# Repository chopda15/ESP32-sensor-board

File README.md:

# ESP32-C3 IoT Sensor Board with Li-ion Power Management

Custom-designed IoT PCB built in KiCad featuring the ESP32-C3-WROOM-02 module, integrated Li-ion charging circuitry, environmental sensing, onboard storage, and USB-C connectivity.

This project was developed to practice real-world embedded hardware design workflows including schematic capture, PCB layout, signal integrity considerations, power management, DFM validation, and manufacturing preparation.

---

# Features

## Microcontroller
- ESP32-C3-WROOM-02
- Wi-Fi + BLE connectivity
- Low-power IoT architecture

## Power System
- TP4056 Li-ion battery charger
- USB-C power input
- Single-cell LiPo battery support
- Battery charging and protection circuitry
- 3.3V regulated power rail

## Sensors & Peripherals
- BME280 environmental sensor
  - Temperature
  - Humidity
  - Pressure
- Ambient light sensor
- Sound sensor with microphone amplifier
- OLED display via I2C
- SPI flash memory
- Micro SD card interface

## User Interface
- Status LEDs
- Push buttons
- USB-UART interface for programming/debugging

---

# PCB Design Highlights

## Signal Integrity
- Differential routing for USB signals
- SPI trace optimization
- Reduced trace lengths for high-speed signals
- Ground plane implementation
- Decoupling capacitor placement optimization

## Power Distribution
- Copper pours for stable power delivery
- Wide power traces to minimize voltage drop
- Multiple decoupling capacitors for noise reduction

## Manufacturing Considerations
- ERC and DRC validation
- DFM analysis before fabrication
- Gerber generation
- BOM and centroid file generation
- Silkscreen refinement
- 3D PCB validation

---

# Tools & Technologies

- KiCad 9
- ESP32-C3
- TP4056
- JLCPCB DFM tools
- Git & GitHub

---

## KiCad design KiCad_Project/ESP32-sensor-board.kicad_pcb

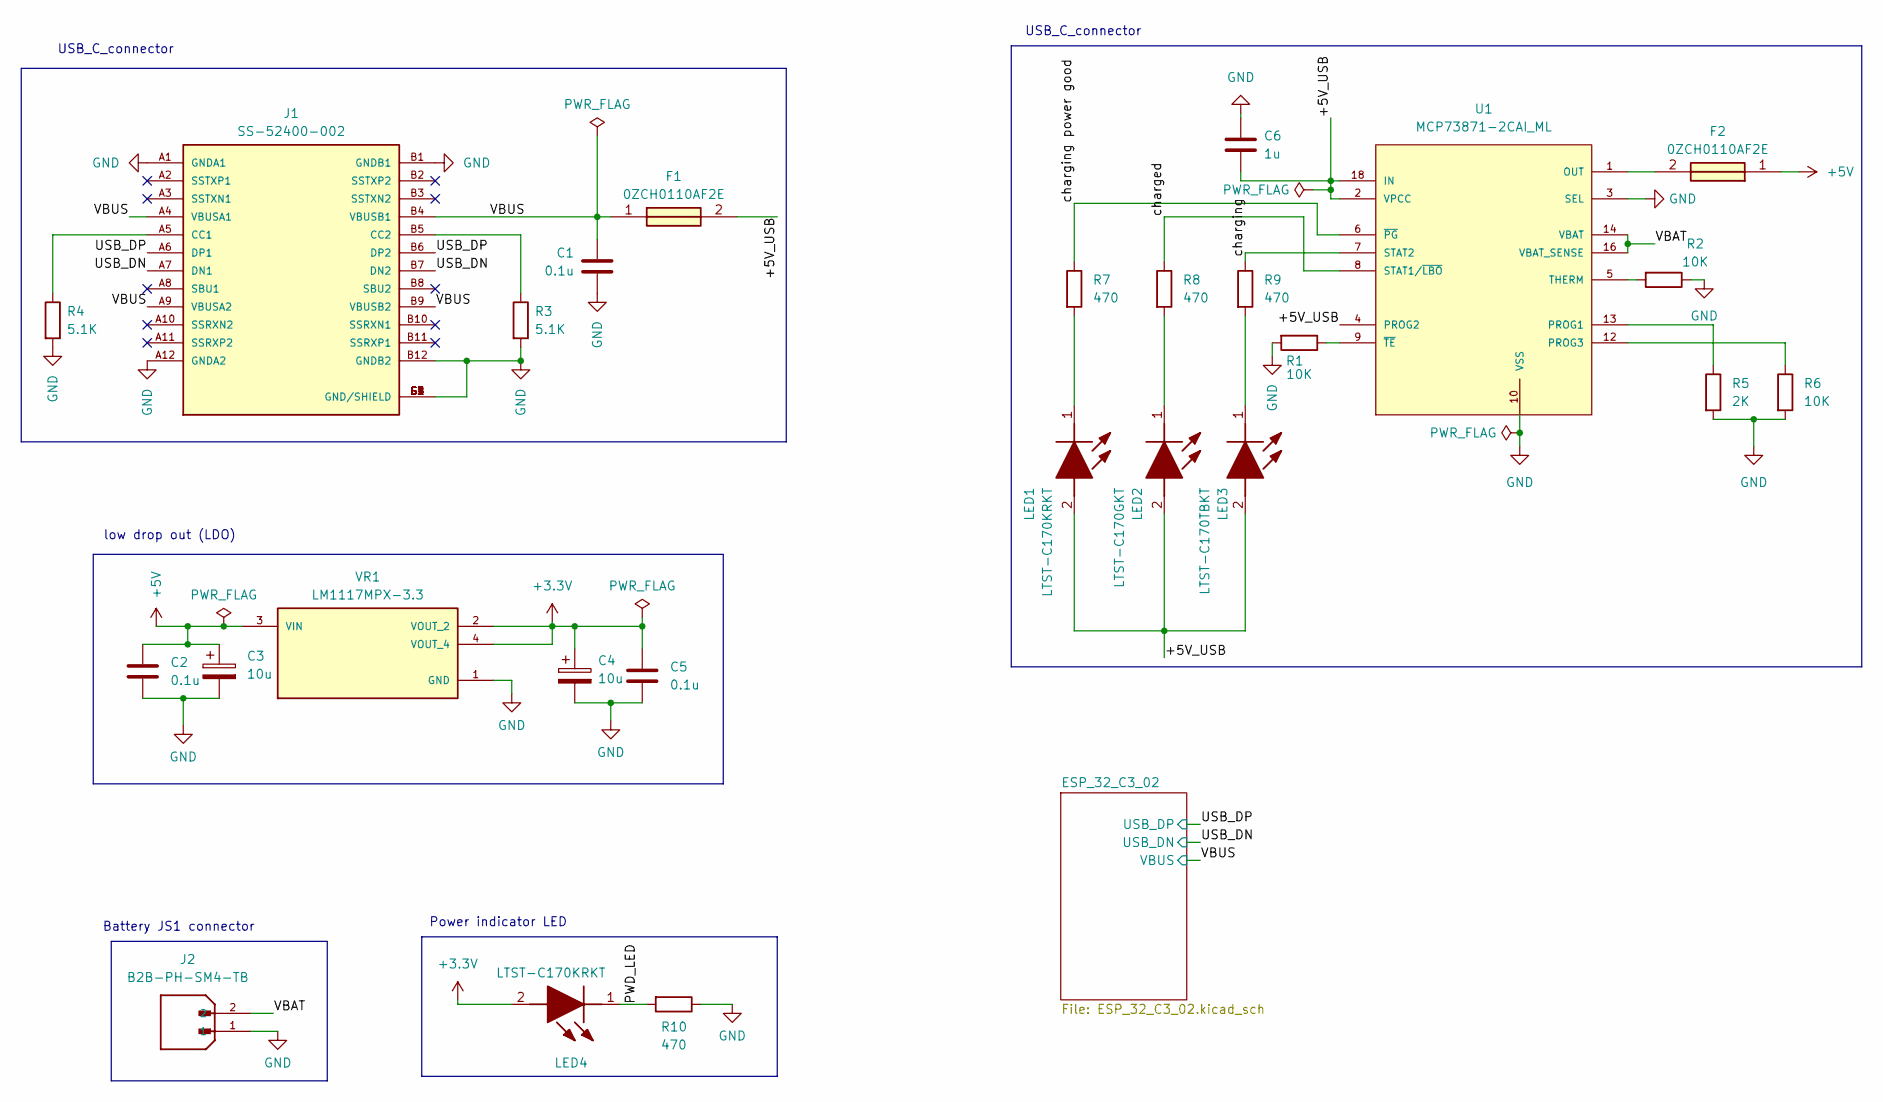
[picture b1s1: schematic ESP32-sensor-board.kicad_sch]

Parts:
C1, C2, C5: 0.1u; C_0805_2012Metric
C3, C4: 10u; T491A
C6: 1u; C_0805_2012Metric
F1, F2: 0ZCH0110AF2E; FUSC3226X100N; Manufacturer_Part_Number 0ZCH0110AF2E
J1: SS-52400-002; BELFUSE_SS-52400-002; PARTREV A0
J2: B2B-PH-SM4-TB; JST_B2B-PH-SM4-TB; PARTREV N/A
LED1, LED4: LTST-C170KRKT; LEDC2012X120N; Manufacturer_Part_Number LTST-C170KRKT; Mouser Part Number 859-LTST-C170KRKT
LED2: LTST-C170GKT; LEDC2012X120N; Manufacturer_Part_Number LTST-C170GKT; Mouser Part Number 859-LTST-C170GKT
LED3: LTST-C170TBKT; LEDC2012X120N; Manufacturer_Part_Number LTST-C170TBKT; Mouser Part Number 859-LTST-C170TBKT
R1, R2, R6: 10K; R_0805_2012Metric
R3, R4: 5.1K; R_0805_2012Metric
R5: 2K; R_0805_2012Metric
R7, R8, R9, R10: 470; R_0805_2012Metric
U1: MCP73871-2CAI_ML; QFN50P400X400X100-21N; PARTREV D
VR1: LM1117MPX-3.3; VREG_LM1117MPX-3.3_NOPB

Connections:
+3.3V: C4.1, C5.1, LED4.2 (A), VR1.2 (VOUT_2), VR1.4 (VOUT_4); also elsewhere on the board
+5V: C2.1, C3.1, F2.1, U1.19, VR1.3 (VIN)
/+5V_USB: C6.2, F1.2, LED1.2 (A), LED2.2 (A), LED3.2 (A), U1.2 (VPCC), U1.4 (PROG2), U1.18 (IN)
/PWD_LED: LED4.1 (K), R10.2
/USB_DN: J1.A7 (DN1), J1.B7 (DN2); also elsewhere on the board
/USB_DP: J1.A6 (DP1), J1.B6 (DP2); also elsewhere on the board
/VBAT: J2.2, U1.14 (VBAT), U1.16 (VBAT_SENSE)
/VBUS: C1.1, F1.1, J1.A4 (VBUSA1), J1.A9 (VBUSA2), J1.B4 (VBUSB1), J1.B9 (VBUSB2); also elsewhere on the board
/charged: R8.1, U1.8 (STAT1/~LBO)
/charging: R9.1, U1.7 (STAT2)
/charging power good: R7.1, U1.6 (~PG)
GND: C1.2, C2.2, C3.2, C4.2, C5.2, C6.1, J1.A1 (GNDA1), J1.A12 (GNDA2), J1.B1 (GNDB1), J1.B12 (GNDB2), J1.G1 (GND/SHIELD), J1.G2 (GND/SHIELD), J1.G3 (GND/SHIELD), J1.G4 (GND/SHIELD), J1.S1 (GND/SHIELD), J1.S2 (GND/SHIELD), J1.S3 (GND/SHIELD), J1.S4 (GND/SHIELD), J2.1, R1.2, R2.1, R3.2, R4.2, R5.2, R6.2, R10.1, U1.3 (SEL), U1.10 (VSS), U1.21, VR1.1 (GND); also elsewhere on the board
unnamed: J1.A5 (CC1), R4.1
unnamed: J1.B5 (CC2), R3.1
unnamed: LED1.1 (K), R7.2
unnamed: LED2.1 (K), R8.2
unnamed: LED3.1 (K), R9.2
unnamed: F2.2, U1.1 (OUT)
unnamed: R5.1, U1.13 (PROG1)
unnamed: R6.1, U1.12 (PROG3)
unnamed: R2.2, U1.5 (THERM)
unnamed: R1.1, U1.9 (~TE)

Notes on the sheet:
USB_C_connector
Battery JS1 connector
low drop out (LDO)
Power indicator LED

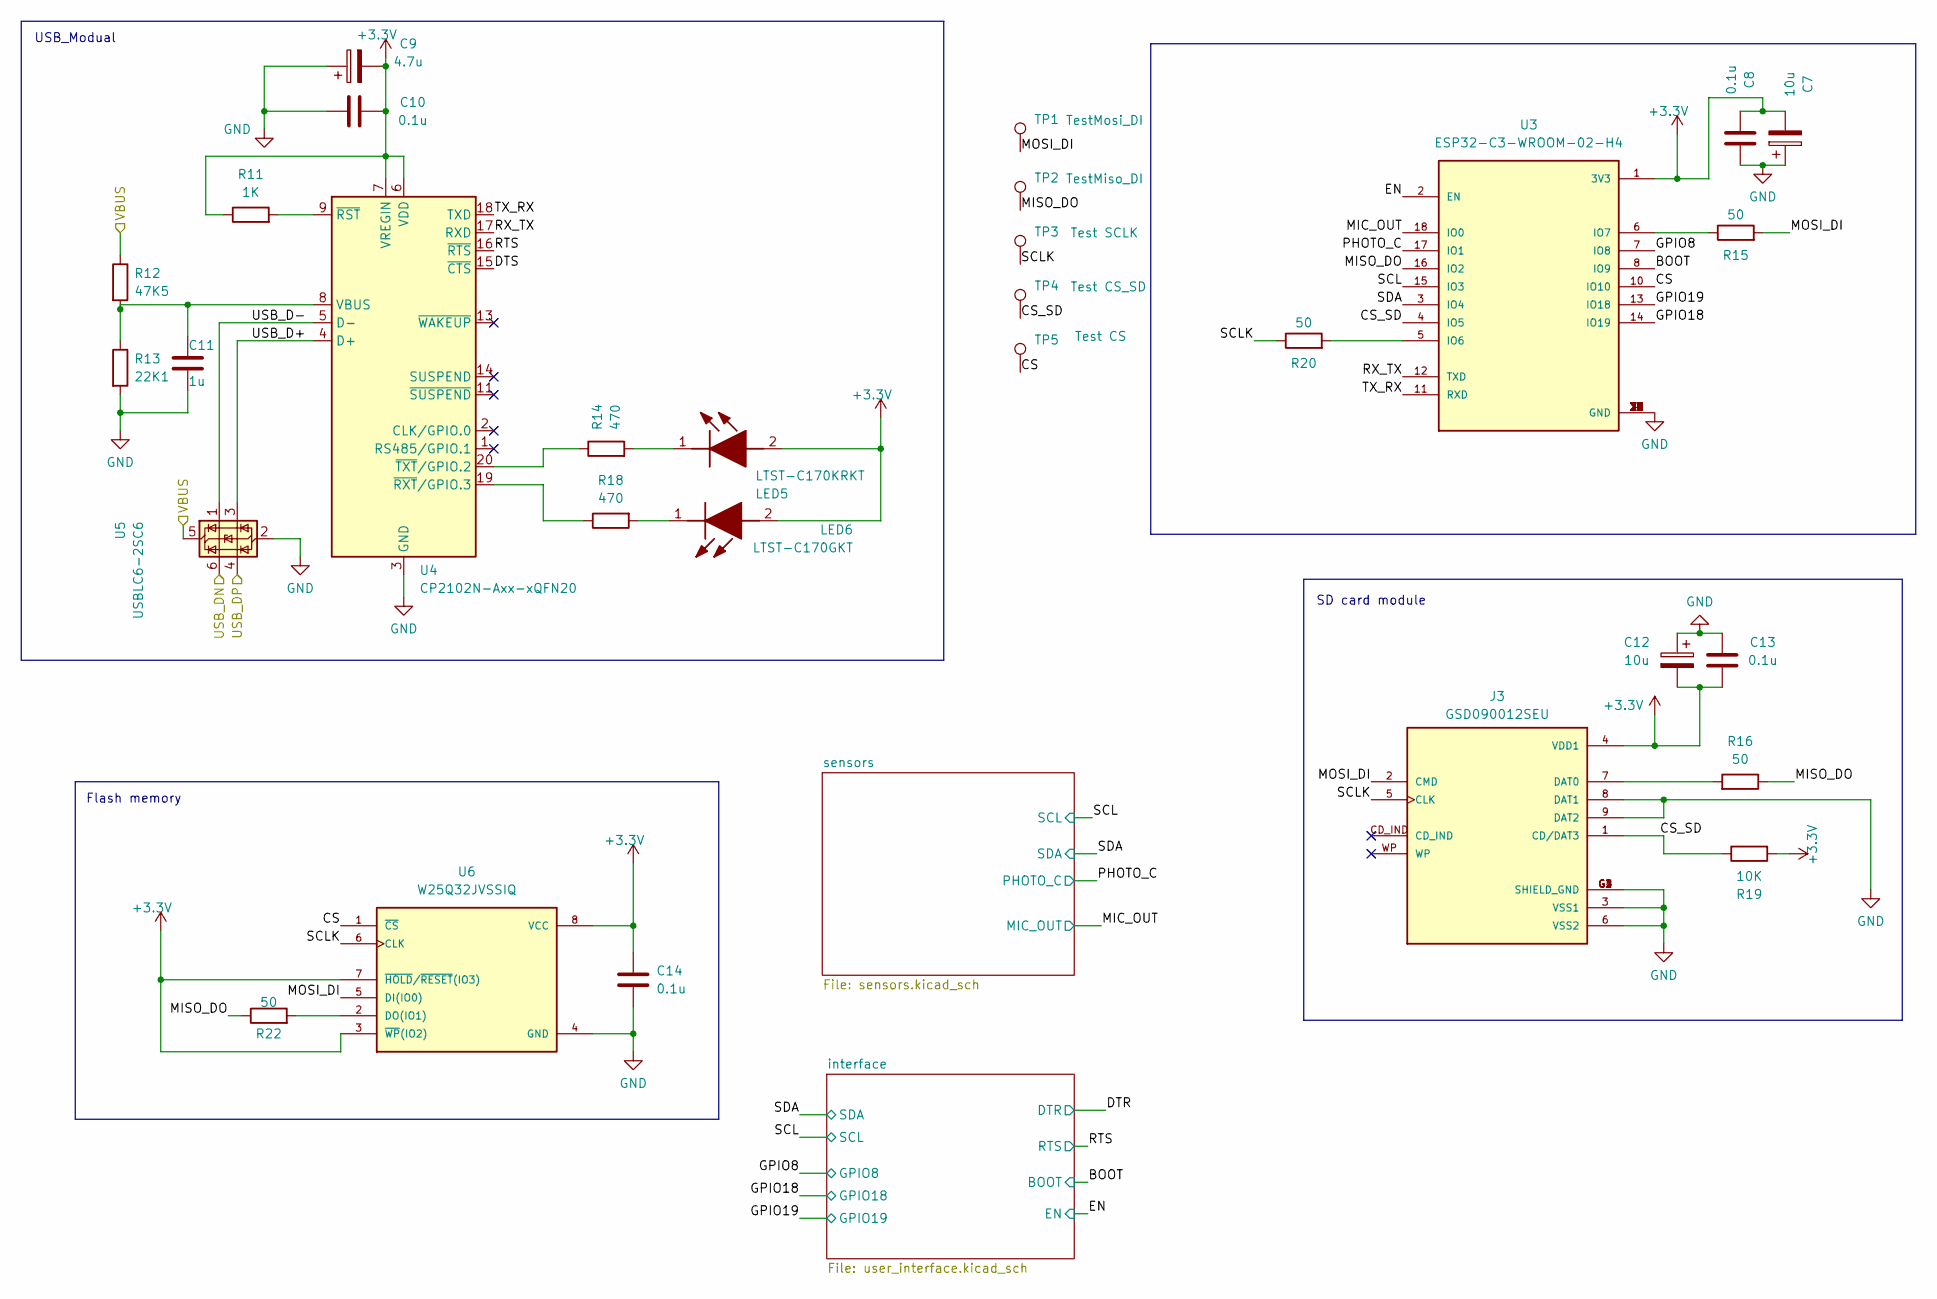
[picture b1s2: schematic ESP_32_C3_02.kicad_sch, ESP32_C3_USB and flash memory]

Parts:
C7, C12: 10u; T491A
C8, C10, C13, C14: 0.1u; C_0805_2012Metric
C9: 4.7u; T491A
C11: 1u; C_0805_2012Metric
J3: GSD090012SEU; AMPHENOL_GSD090012SEU; PARTREV E
LED5: LTST-C170KRKT; LEDC2012X120N; Manufacturer_Part_Number LTST-C170KRKT; Mouser Part Number 859-LTST-C170KRKT
LED6: LTST-C170GKT; LEDC2012X120N; Manufacturer_Part_Number LTST-C170GKT; Mouser Part Number 859-LTST-C170GKT
R11: 1K; R_0805_2012Metric
R12: 47K5; R_0805_2012Metric
R13: 22K1; R_0805_2012Metric
R14, R18: 470; R_0805_2012Metric
R15, R16, R20, R22: 50; R_0805_2012Metric
R19: 10K; R_0805_2012Metric
TP1: TestMosi_DI; TestPoint_Pad_D1.0mm
TP2: TestMiso_DI; TestPoint_Pad_D1.0mm
TP3: Test SCLK; TestPoint_Pad_D1.0mm
TP4: Test CS_SD; TestPoint_Pad_D1.0mm
TP5: Test CS; TestPoint_Pad_D1.0mm
U3: ESP32-C3-WROOM-02-H4; MODULE_ESP32-C3-WROOM-02-H4
U4: CP2102N-Axx-xQFN20; SiliconLabs_QFN-20-1EP_3x3mm_P0.5mm_EP1.8x1.8mm
U5: USBLC6-2SC6; SOT-23-6
U6: W25Q32JVSSIQ; SOIC127P790X216-8N; M_PART_NUMBER W25QXX

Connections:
+3.3V: C7.2, C8.2, C9.2, C10.2, C12.2, C13.2, C14.1, J3.4 (VDD1), LED5.2 (A), LED6.2 (A), R11.1, R19.2, U3.1 (3V3), U4.6 (VDD), U4.7 (VREGIN), U6.3 (~WP(IO2)), U6.7 (~HOLD/~RESET(IO3)), U6.8 (VCC); also elsewhere on the board
/ESP_32_C3_02/BOOT: U3.8 (IO9); also elsewhere on the board
/ESP_32_C3_02/CS: TP5.1 (1_1), U3.10 (IO10), U6.1 (~CS)
/ESP_32_C3_02/CS_SD: J3.1 (CD/DAT3), R19.1, TP4.1 (1_1), U3.4 (IO5)
/ESP_32_C3_02/DTS: U4.15 (~CTS)
/ESP_32_C3_02/EN: U3.2 (EN); also elsewhere on the board
/ESP_32_C3_02/GPIO8: U3.7 (IO8); also elsewhere on the board
/ESP_32_C3_02/GPIO18: U3.14 (IO19); also elsewhere on the board
/ESP_32_C3_02/GPIO19: U3.13 (IO18); also elsewhere on the board
/ESP_32_C3_02/MIC_OUT: U3.18 (IO0); also elsewhere on the board
/ESP_32_C3_02/MISO_DO: R16.1, R22.1, TP2.1 (1_1), U3.16 (IO2)
/ESP_32_C3_02/MOSI_DI: J3.2 (CMD), R15.2, TP1.1 (1_1), U6.5 (DI(IO0))
/ESP_32_C3_02/PHOTO_C: U3.17 (IO1); also elsewhere on the board
/ESP_32_C3_02/RTS: U4.16 (~RTS); also elsewhere on the board
/ESP_32_C3_02/RX_TX: U3.12 (TXD), U4.17 (RXD)
/ESP_32_C3_02/SCL: U3.15 (IO3); also elsewhere on the board
/ESP_32_C3_02/SCLK: J3.5 (CLK), R20.1, TP3.1 (1_1), U6.6 (CLK)
/ESP_32_C3_02/SDA: U3.3 (IO4); also elsewhere on the board
/ESP_32_C3_02/TX_RX: U3.11 (RXD), U4.18 (TXD)
/ESP_32_C3_02/USB_D+: U4.4 (D+), U5.3 (I/O2)
/ESP_32_C3_02/USB_D-: U4.5 (D-), U5.1 (I/O1)
/USB_DN: U5.6 (I/O1); also elsewhere on the board
/USB_DP: U5.4 (I/O2); also elsewhere on the board
/VBUS: R12.1, U5.5 (VBUS); also elsewhere on the board
GND: C7.1, C8.1, C9.1, C10.1, C11.2, C12.1, C13.1, C14.2, J3.3 (VSS1), J3.6 (VSS2), J3.8 (DAT1), J3.9 (DAT2), J3.G1 (SHIELD_GND), J3.G2 (SHIELD_GND), J3.G3 (SHIELD_GND), J3.G4 (SHIELD_GND), R13.2, U3.9 (GND), U3.19 (GND), U3.20 (GND), U3.21 (GND), U3.22 (GND), U3.23 (GND), U3.24 (GND), U3.25 (GND), U3.26 (GND), U3.27 (GND), U3.28 (GND), U3.29 (GND), U3.30 (GND), U3.31 (GND), U3.32 (GND), U3.33 (GND), U3.34 (GND), U3.35 (GND), U3.36 (GND), U3.37 (GND), U3.38 (GND), U3.39 (GND), U4.3 (GND), U4.12 (GND), U4.21 (GND), U5.2 (GND), U6.4 (GND); also elsewhere on the board
unnamed: J3.7 (DAT0), R16.2
unnamed: LED5.1 (K), R14.2
unnamed: LED6.1 (K), R18.2
unnamed: R20.2, U3.5 (IO6)
unnamed: R15.1, U3.6 (IO7)
unnamed: C11.1, R12.2, R13.1, U4.8 (VBUS)
unnamed: R11.2, U4.9 (~RST)
unnamed: R18.1, U4.19 (~RXT/GPIO.3)
unnamed: R14.1, U4.20 (~TXT/GPIO.2)
unnamed: R22.2, U6.2 (DO(IO1))

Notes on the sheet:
USB_Modual
SD card module
Flash memory

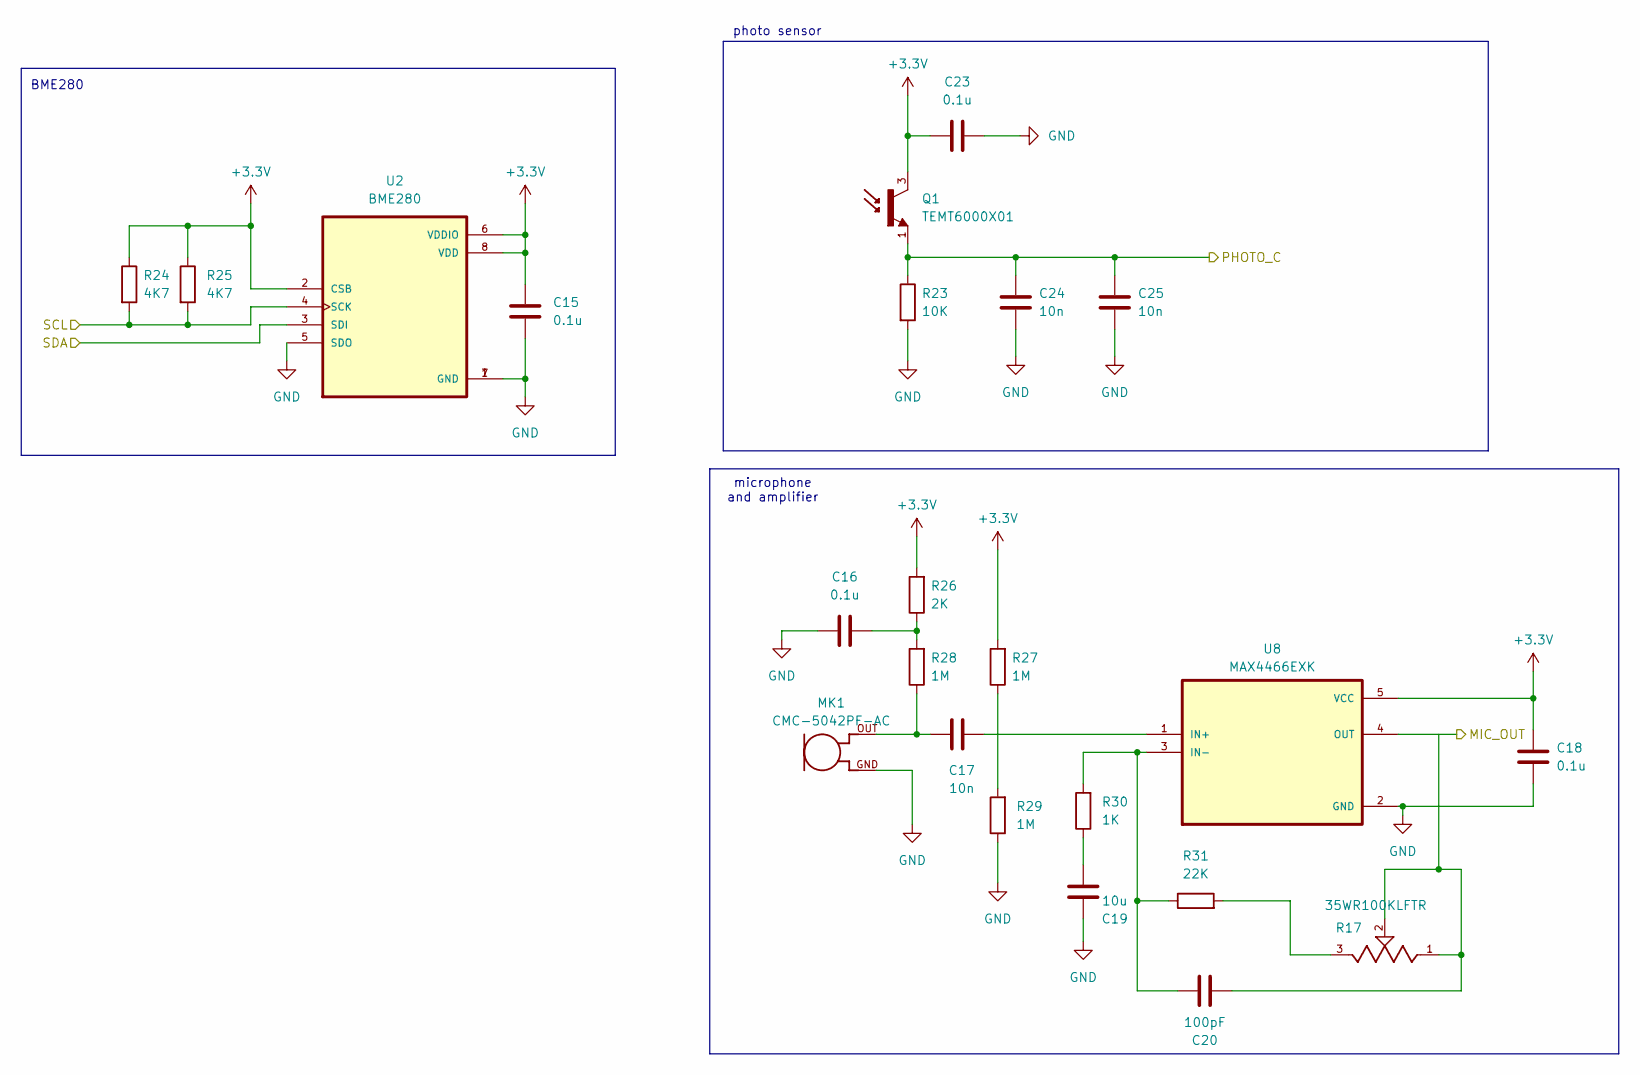
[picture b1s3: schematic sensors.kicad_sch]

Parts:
C15, C16, C18, C23: 0.1u; C_0805_2012Metric
C17, C24, C25: 10n; C_0805_2012Metric
C19: 10u; C_0805_2012Metric
C20: 100pF; C_0805_2012Metric
MK1: CMC-5042PF-AC; CUI_CMC-5042PF-AC
Q1: TEMT6000X01; TRANS_TEMT6000X01; PARTREV 1.9
R17: 35WR100KLFTR; TRIM_35WR100KLFTR; PARTREV D
R23: 10K; R_0805_2012Metric
R24, R25: 4K7; R_0805_2012Metric
R26: 2K; R_0805_2012Metric
R27, R28, R29: 1M; R_0805_2012Metric
R30: 1K; R_0805_2012Metric
R31: 22K; R_0805_2012Metric
U2: BME280; PSON65P250X250X100-8N
U8: MAX4466EXK; SOT65P210X110-5N

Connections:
+3.3V: C15.1, C18.1, C23.1, Q1.3, R24.1, R25.1, R26.2, R27.2, U2.2 (CSB), U2.6 (VDDIO), U2.8 (VDD), U8.5 (VCC); also elsewhere on the board
/ESP_32_C3_02/MIC_OUT: U8.4 (OUT); also elsewhere on the board
/ESP_32_C3_02/PHOTO_C: C24.2, C25.2, Q1.1, R23.1; also elsewhere on the board
/ESP_32_C3_02/SCL: R24.2, R25.2, U2.4 (SCK); also elsewhere on the board
/ESP_32_C3_02/SDA: U2.3 (SDI); also elsewhere on the board
GND: C15.2, C16.1, C18.2, C19.2, C23.2, C24.1, C25.1, MK1.GND, R23.2, R29.1, U2.1 (GND), U2.5 (SDO), U2.7 (GND), U8.2 (GND); also elsewhere on the board
unnamed: C16.2, R26.1, R28.2
unnamed: C17.1, MK1.OUT, R28.1
unnamed: C19.1, R30.1
unnamed: C20.2, R17.1, R17.2
unnamed: R17.3, R31.2
unnamed: R27.1, R29.2
unnamed: C17.2, U8.1 (IN+)
unnamed: C20.1, R30.2, R31.1, U8.3 (IN-)

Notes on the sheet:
BME280
microphone and amplifier
photo sensor

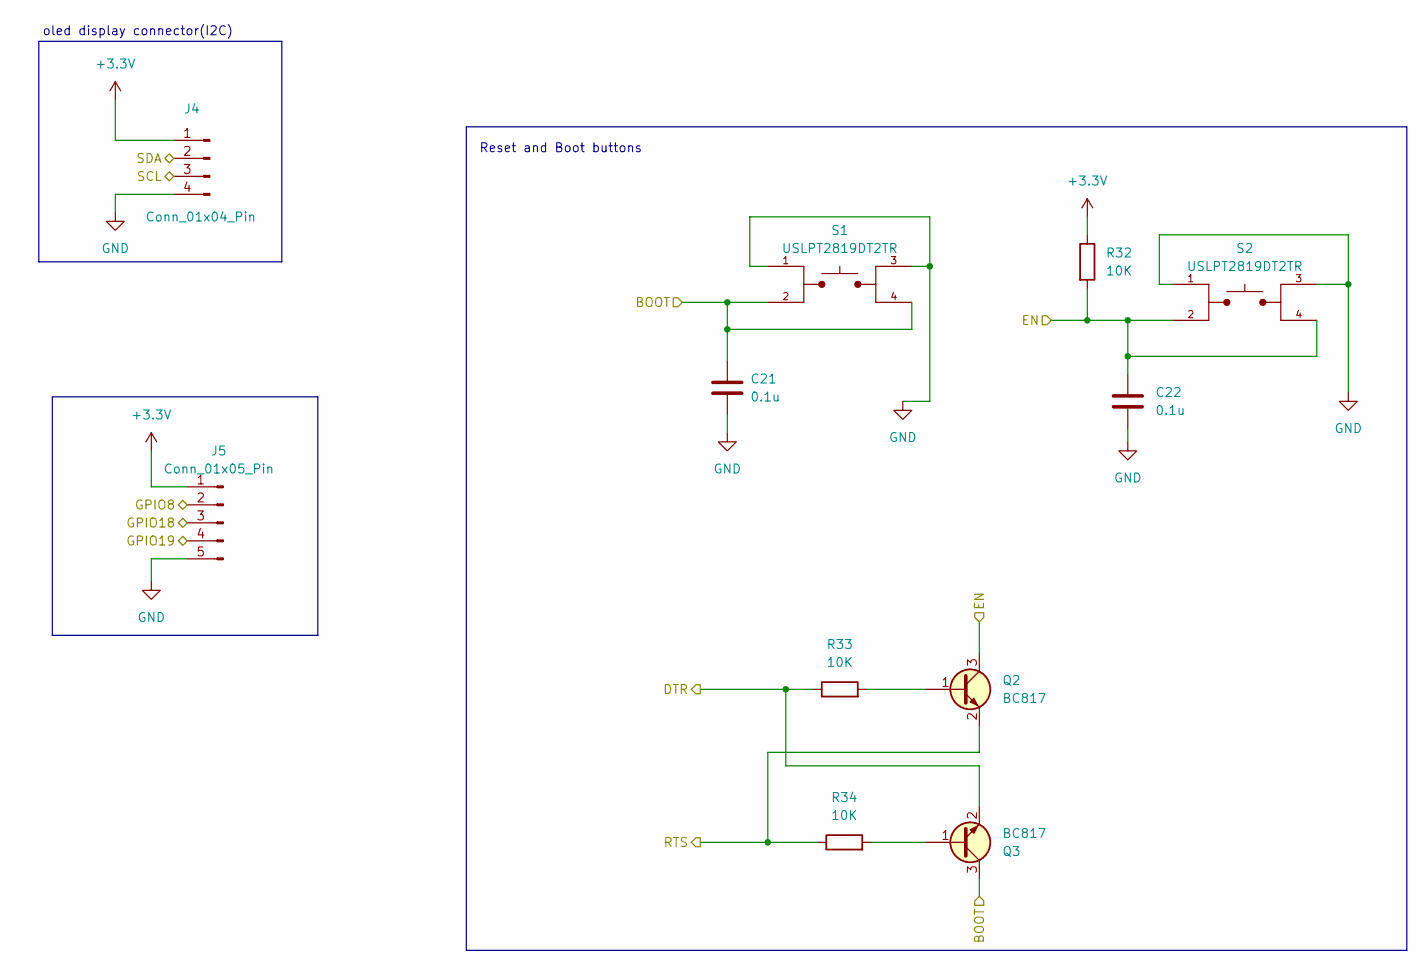
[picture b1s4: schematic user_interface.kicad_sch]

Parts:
C21, C22: 0.1u; C_0805_2012Metric
J4: Conn_01x04_Pin; PinHeader_1x04_P2.54mm_Vertical
J5: Conn_01x05_Pin; PinHeader_1x05_P2.54mm_Vertical
Q2, Q3: BC817; SOT-23
R32, R33, R34: 10K; R_0805_2012Metric
S1, S2: USLPT2819DT2TR; SW_TL3305AF260QG; PARTREV C

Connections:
+3.3V: J4.1, J5.1, R32.1; also elsewhere on the board
/ESP_32_C3_02/BOOT: C21.1, Q3.3 (C), S1.2, S1.4; also elsewhere on the board
/ESP_32_C3_02/DTR: Q3.2 (E), R33.1
/ESP_32_C3_02/EN: C22.1, Q2.3 (C), R32.2, S2.2, S2.4; also elsewhere on the board
/ESP_32_C3_02/GPIO8: J5.2; also elsewhere on the board
/ESP_32_C3_02/GPIO18: J5.3; also elsewhere on the board
/ESP_32_C3_02/GPIO19: J5.4; also elsewhere on the board
/ESP_32_C3_02/RTS: Q2.2 (E), R34.1; also elsewhere on the board
/ESP_32_C3_02/SCL: J4.3; also elsewhere on the board
/ESP_32_C3_02/SDA: J4.2; also elsewhere on the board
GND: C21.2, C22.2, J4.4, J5.5, S1.1, S1.3, S2.1, S2.3; also elsewhere on the board
unnamed: Q2.1 (B), R33.2
unnamed: Q3.1 (B), R34.2

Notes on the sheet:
Reset and Boot buttons
oled display connector(I2C)

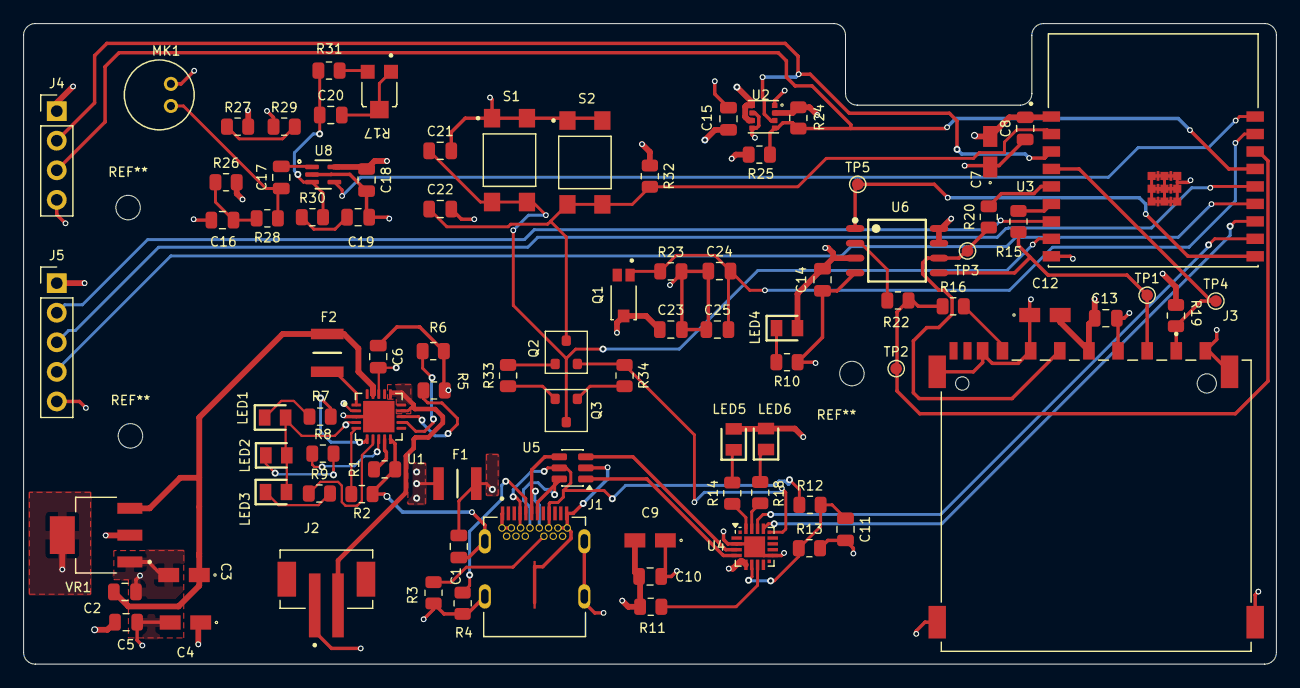
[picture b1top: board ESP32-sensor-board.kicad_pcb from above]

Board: 4 copper layers, 107.6 x 55.0 mm, 90 parts (0 on the bottom side), 62 nets.

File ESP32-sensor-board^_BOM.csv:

"Reference","Qty","Value","DNP","Exclude from BOM","Exclude from Board","Footprint","Datasheet"
"C1,C2,C5,C8,C10,C13,C14,C15,C16,C18,C21,C22,C23","13","0.1u","","","","Capacitor_SMD:C_0805_2012Metric",""
"C3,C4,C7,C12","4","10u","","","","Footprints:T491A",""
"C6,C11","2","1u","","","","Capacitor_SMD:C_0805_2012Metric",""
"C9","1","4.7u","","","","Footprints:T491A",""
"C17,C24,C25","3","10n","","","","Capacitor_SMD:C_0805_2012Metric",""
"C19","1","10u","","","","Capacitor_SMD:C_0805_2012Metric",""
"C20","1","100pF","","","","Capacitor_SMD:C_0805_2012Metric",""
"F1,F2","2","0ZCH0110AF2E","","","","Footprints:FUSC3226X100N","https://www.belfuse.com/resources/datasheets/circuitprotecti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"
"J1","1","SS-52400-002","","","","Footprints:BELFUSE_SS-52400-002",""
"J2","1","B2B-PH-SM4-TB","","","","Footprints:JST_B2B-PH-SM4-TB",""
"J3","1","GSD090012SEU","","","","Footprints:AMPHENOL_GSD090012SEU",""
"J4","1","Conn_01x04_Pin","","","","Connector_PinHeader_2.54mm:PinHeader_1x04_P2.54mm_Vertical",""
"J5","1","Conn_01x05_Pin","","","","Connector_PinHeader_2.54mm:PinHeader_1x05_P2.54mm_Vertical",""
"LED1,LED4,LED5","3","LTST-C170KRKT","","","","Footprints:LEDC2012X120N","https://componentsearchengine.com/Datasheets/1/LTST-C170KRKT.pdf"
"LED2,LED6","2","LTST-C170GKT","","","","Footprints:LEDC2012X120N","https://mm.digikey.com/Volume0/opasdata/d220001/medias/docus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"
"LED3","1","LTST-C170TBKT","","","","Footprints:LEDC2012X120N","https://componentsearchengine.com/Datasheets/1/LTST-C170TBKT.pdf"
"MK1","1","CMC-5042PF-AC","","","","Footprints:CUI_CMC-5042PF-AC",""
"Q1","1","TEMT6000X01","","","","Footprints:TRANS_TEMT6000X01",""
"Q2,Q3","2","BC817","","","","PCM_Package_TO_SOT_SMD_AKL:SOT-23","https://www.tme.eu/Document/7b5ea7386544f524d0315334956093bb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"
"R1,R2,R6,R19,R23,R32,R33,R34","8","10K","","","","Resistor_SMD:R_0805_2012Metric",""
"R3,R4","2","5.1K","","","","Resistor_SMD:R_0805_2012Metric",""
"R5,R26","2","2K","","","","Resistor_SMD:R_0805_2012Metric",""
"R7,R8,R9,R10,R14,R18","6","470","","","","Resistor_SMD:R_0805_2012Metric",""
"R11,R30","2","1K","","","","Resistor_SMD:R_0805_2012Metric",""
"R12","1","47K5","","","","Resistor_SMD:R_0805_2012Metric",""
"R13","1","22K1","","","","Resistor_SMD:R_0805_2012Metric",""
"R15,R16,R20,R22","4","50","","","","Resistor_SMD:R_0805_2012Metric",""
"R17","1","35WR100KLFTR","","","","Footprints:TRIM_35WR100KLFTR",""
"R24,R25","2","4K7","","","","Resistor_SMD:R_0805_2012Metric",""
"R27,R28,R29","3","1M","","","","Resistor_SMD:R_0805_2012Metric",""
"R31","1","22K","","","","Resistor_SMD:R_0805_2012Metric",""
"S1,S2","2","USLPT2819DT2TR","","","","Footprints:SW_TL3305AF260QG",""
"TP1","1","TestMosi_DI","","","","TestPoint:TestPoint_Pad_D1.0mm",""
"TP2","1","TestMiso_DI","","","","TestPoint:TestPoint_Pad_D1.0mm",""
"TP3","1","Test SCLK","","","","TestPoint:TestPoint_Pad_D1.0mm",""
"TP4","1","Test CS_SD","","","","TestPoint:TestPoint_Pad_D1.0mm",""
"TP5","1","Test CS","","","","TestPoint:TestPoint_Pad_D1.0mm",""
"U1","1","MCP73871-2CAI_ML","","","","Footprints:QFN50P400X400X100-21N",""
"U2","1","BME280","","","","Footprints:PSON65P250X250X100-8N",""
"U3","1","ESP32-C3-WROOM-02-H4","","","","Footprints:MODULE_ESP32-C3-WROOM-02-H4",""
"U4","1","CP2102N-Axx-xQFN20","","","","Package_DFN_QFN:SiliconLabs_QFN-20-1EP_3x3mm_P0.5mm_EP1.8x1.8mm","https://www.silabs.com/documents/public/data-sheets/cp2102n-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"
"U5","1","USBLC6-2SC6","","","","Package_TO_SOT_SMD:SOT-23-6","https://www.st.com/resource/en/datasheet/usblc6-2.pdf"
"U6","1","W25Q32JVSSIQ","","","","Footprints:SOIC127P790X216-8N",""
"U8","1","MAX4466EXK","","","","Footprints:SOT65P210X110-5N",""
"VR1","1","LM1117MPX-3.3","","","","Footprints:VREG_LM1117MPX-3.3_NOPB",""

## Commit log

2026-06-07 ESP32
    ESP32 added to github
2026-06-07 Initialize README with project overview and features
    Add detailed project description and features for the ESP32-C3 IoT Sensor Board, including PCB design highlights and repository structure.
2026-06-07 removed text
2026-06-07 Add common patterns to .gitignore
2026-06-08 Add root gitignore for KiCad project files
